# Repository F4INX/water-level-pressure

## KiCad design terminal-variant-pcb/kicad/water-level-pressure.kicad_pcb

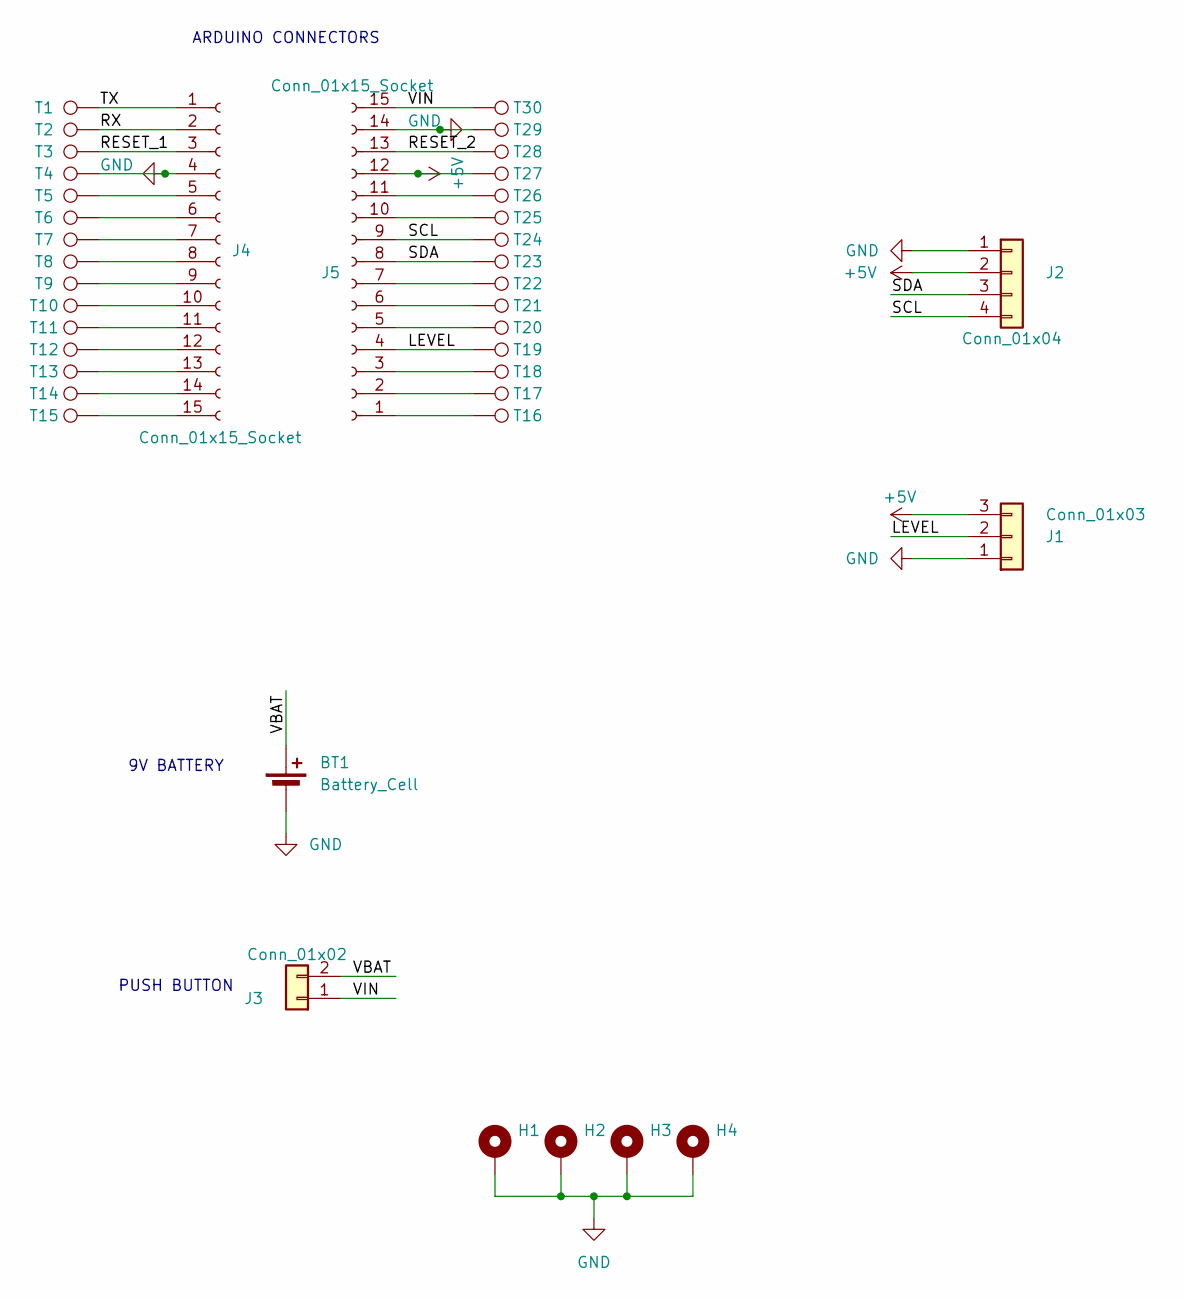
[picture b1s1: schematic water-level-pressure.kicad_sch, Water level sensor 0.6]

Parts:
BT1: Battery_Cell; BatteryHolder_MPD_BA9VPC_1xPP3; LCSC C5556545
H1, H2, H3, H4: MountingHole_Pad; MountingHole_4.3mm_M4_Pad_TopBottom
J1: Conn_01x03; TerminalBlock_Phoenix_MPT-0,5-3-2.54_1x03_P2.54mm_Horizontal; LCSC C691850
J2: Conn_01x04; PinHeader_1x04_P2.54mm_Vertical; LCSC C124378
J3: Conn_01x02; TerminalBlock_Phoenix_MPT-0,5-2-2.54_1x02_P2.54mm_Horizontal; LCSC C699496
J4, J5: Conn_01x15_Socket; PinSocket_1x15_P2.54mm_Vertical; LCSC C124408
T1, T2, T3, T4, T5, T6, T7, T8, T9, T10, T11, T12, T13, T14, T15, T16, T17, T18, T19, T20, T21, T22, T23, T24, T25, T26, T27, T28, T29, T30: TestPoint; TestPoint_THTPad_D1.6mm_Drill1.0mm_Variant

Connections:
+5V: J1.3, J2.2, J5.12, T27.1 (1_1)
/LEVEL: J1.2, J5.4, T19.1 (1_1)
/RESET_1: J4.3, T3.1 (1_1)
/RESET_2: J5.13, T28.1 (1_1)
/RX: J4.2, T2.1 (1_1)
/SCL: J2.4, J5.9, T24.1 (1_1)
/SDA: J2.3, J5.8, T23.1 (1_1)
/TX: J4.1, T1.1 (1_1)
/VBAT: BT1.1 (+), J3.2
/VIN: J3.1, J5.15, T30.1 (1_1)
GND: BT1.2 (-), H1.1 (1_1), H2.1 (1_1), H3.1 (1_1), H4.1 (1_1), J1.1, J2.1, J4.4, J5.14, T4.1 (1_1), T29.1 (1_1)
unnamed: J4.5, T5.1 (1_1)
unnamed: J4.6, T6.1 (1_1)
unnamed: J4.7, T7.1 (1_1)
unnamed: J4.8, T8.1 (1_1)
unnamed: J4.9, T9.1 (1_1)
unnamed: J4.10, T10.1 (1_1)
unnamed: J4.11, T11.1 (1_1)
unnamed: J4.12, T12.1 (1_1)
unnamed: J4.13, T13.1 (1_1)
unnamed: J4.14, T14.1 (1_1)
unnamed: J4.15, T15.1 (1_1)
unnamed: J5.1, T16.1 (1_1)
unnamed: J5.2, T17.1 (1_1)
unnamed: J5.3, T18.1 (1_1)
unnamed: J5.5, T20.1 (1_1)
unnamed: J5.6, T21.1 (1_1)
unnamed: J5.7, T22.1 (1_1)
unnamed: J5.10, T25.1 (1_1)
unnamed: J5.11, T26.1 (1_1)

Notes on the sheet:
9V BATTERY
PUSH BUTTON
ARDUINO CONNECTORS

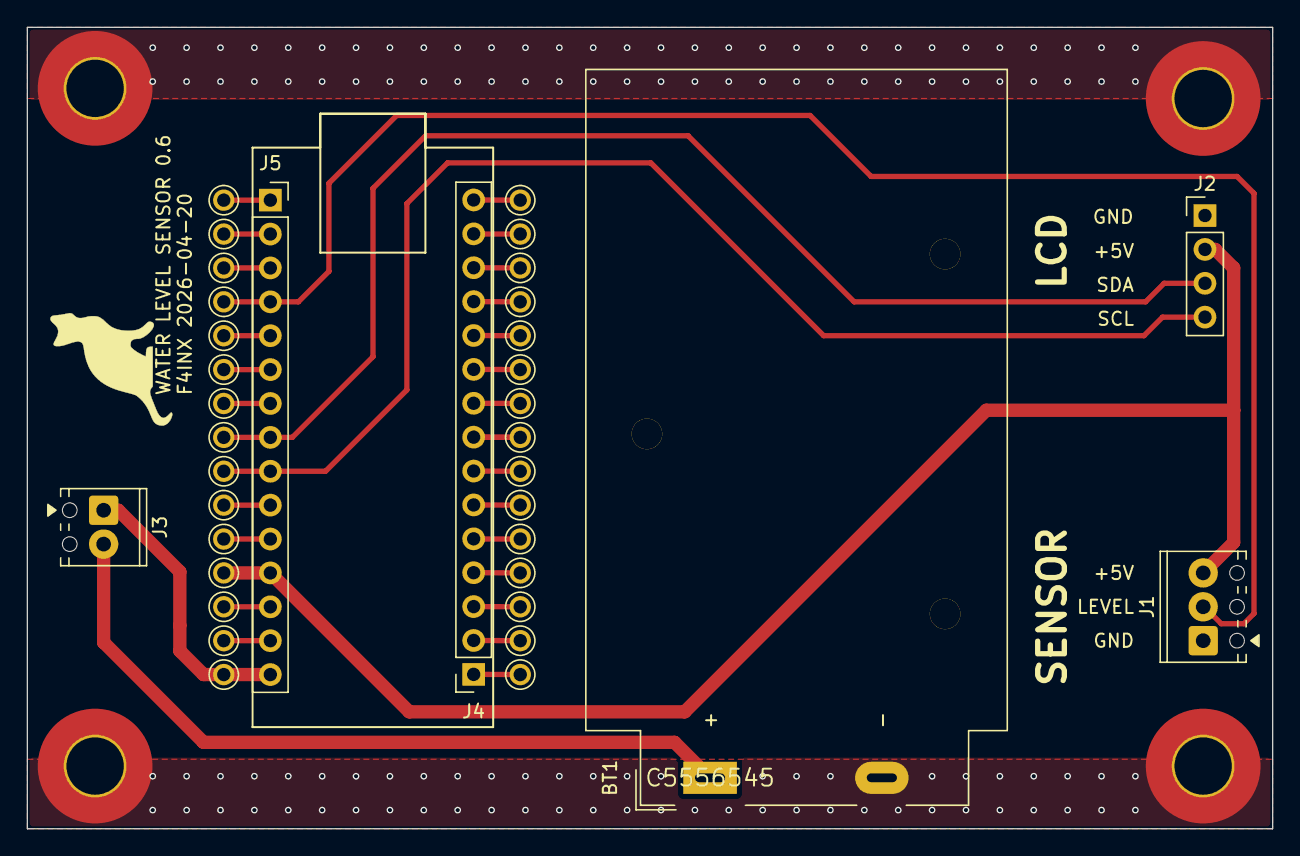
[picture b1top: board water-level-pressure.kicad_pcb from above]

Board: 2 copper layers, 93.3 x 60.1 mm, 40 parts (0 on the bottom side), 30 nets.

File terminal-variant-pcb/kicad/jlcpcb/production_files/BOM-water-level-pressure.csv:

Comment,Designator,Footprint,LCSC,Quantity
Battery_Cell,BT1,BatteryHolder_MPD_BA9VPC_1xPP3,C5556545,1
Conn_01x02,J3,"TerminalBlock_Phoenix_MPT-0,5-2-2.54_1x02_P2.54mm_Horizontal",C699496,1
Conn_01x03,J1,"TerminalBlock_Phoenix_MPT-0,5-3-2.54_1x03_P2.54mm_Horizontal",C691850,1
Conn_01x04,J2,PinHeader_1x04_P2.54mm_Vertical,C124378,1
Conn_01x15_Socket,"J4,J5",PinSocket_1x15_P2.54mm_Vertical,C124408,2

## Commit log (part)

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2026-01-07 List of sensors, draft on tests.
2026-01-07 Ordered a sensor and update prices.
2026-01-17 Add implantation pictures.
2026-02-01 Add unboxing pictures.
2026-02-01 First tests of sensor.
2026-02-01 Second tests, sensor broken.
2026-02-09 Begin of isolated connections.
2026-02-10 Add cables to connect to supply.
2026-02-10 New order, update sensor price.
2026-02-10 Precise selected indicator to isolated-connections.txt.
2026-02-20 Add pictures of isolated cables and connectors.
2026-02-24 Tests performed and successful.
2026-02-28 Backup useful icons.
2026-02-28 First draft of schematic.
2026-03-01 Continue schematic.
2026-03-17 First outline of PCB variant.
2026-03-17 First draft of PCB.
2026-03-17 Add 9V battery holder.
2026-03-17 Remove old draft and move PCB files.
2026-03-17 Update JLCPCB manufacturing files.
2026-03-17 Remove the only SMD component to avoid cost.
2026-03-17 Add terminal block for sensor and update price.
2026-03-17 Add terminal block for puch button and update price.
2026-03-17 Replacing Arduino footprint by pair of connectors footprints.
2026-03-17 Add LCD connector. First draft. Update PDF schematic. Remove old SVG schematic.
2026-03-17 Add LCSC for LCD header.
2026-03-17 Remove mounting holes from assembly files.
2026-03-17 Add JLCPCB price.
2026-03-17 Change battery holder assembly from JLCPCB to manual.
2026-03-17 Update PCB picture.
2026-03-17 Add 3D view.
2026-03-28 Version 0.2 following Gönül Demir's review. Simplified routing without crossings. No trace between pads for clearance. Increase supplies thickness to 1 mm. Fix thickness of one of the Arduino to pads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
2026-03-28 Version 0.3 following Gönül Demir's review. Fix thickness of 5V line between Arduino and pads. Route SDA and SCL together, in the same side of the hole.
2026-03-28 Version 0.4. Slight ptimisation of 5V routing. 5V trace outside of silkscreen. LCD silkscreen outside of SDA trace. Raytracing for 3D view.
2026-03-28 Version 0.5. Fix connectors orientation. Fix title in schematic (was title of old version using ultrasonic). Fix pads footprints paths (was old ultrasonic).
2026-03-31 Update JLCPCB files for version 0.5. Fix connectors JLCPCB position and orientation. Add battery holder for JLCPCB. Fix battery holder JLCPCB position. Update price.
2026-03-31 Add final invoice.
2026-03-31 List of possible LCDs.
2026-04-01 Link to order Arduino board.
2026-04-01 Link to Dupont cables.
2026-04-01 Final order and price update.
2026-04-19 Pictures of unboxing of PCBs.
2026-04-20 Found and workaround for mistake in PCB.
2026-04-20 LCD integration and PlatformIO.
2026-04-20 Sensor read test.
2026-04-20 Fix ADC formula.
2026-04-20 Use bandgap because USB 5V not precise (diode drop).
2026-04-20 Show depth instead of voltage.
2026-04-20 Cleanup + serial output for debug.
2026-04-20 Disable useless stuff for production.
2026-04-20 Consumption investigation.
